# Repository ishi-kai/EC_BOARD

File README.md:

# This Board for Electrochromic Device Workshop.

- [Electrochromic Device Workshop:PDF](https://ishi-kai.org/assets/pdf/EC.pdf)
- [Electrochromic Device Workshop:PPTX](https://ishi-kai.org/assets/pdf/EC.pptx)

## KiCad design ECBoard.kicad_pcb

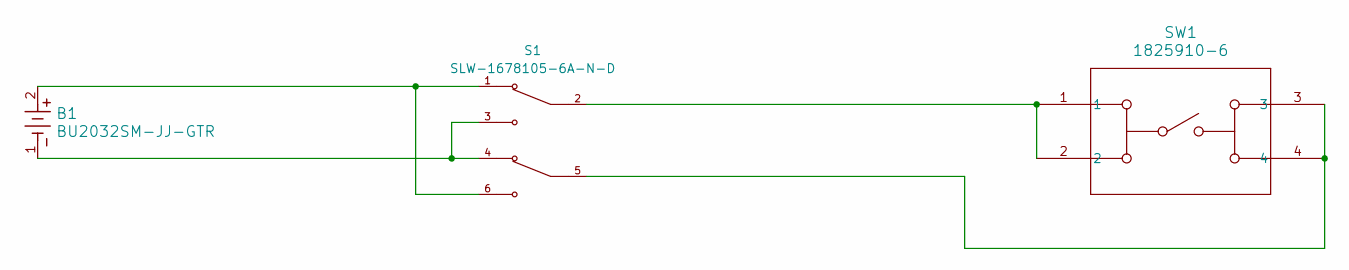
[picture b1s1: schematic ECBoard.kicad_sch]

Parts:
B1: BU2032SM-JJ-GTR; BU2032SM-JJ-GTR_MPD
S1: SLW-1678105-6A-N-D; SW_SLW-1678105-6A-N-D; PARTREV 1.01
SW1: 1825910-6; SW4_1825910-B_TEC

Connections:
unnamed: B1.1, S1.3, S1.4
unnamed: B1.2, S1.1, S1.6
unnamed: S1.2, SW1.1, SW1.2
unnamed: S1.5, SW1.3, SW1.4

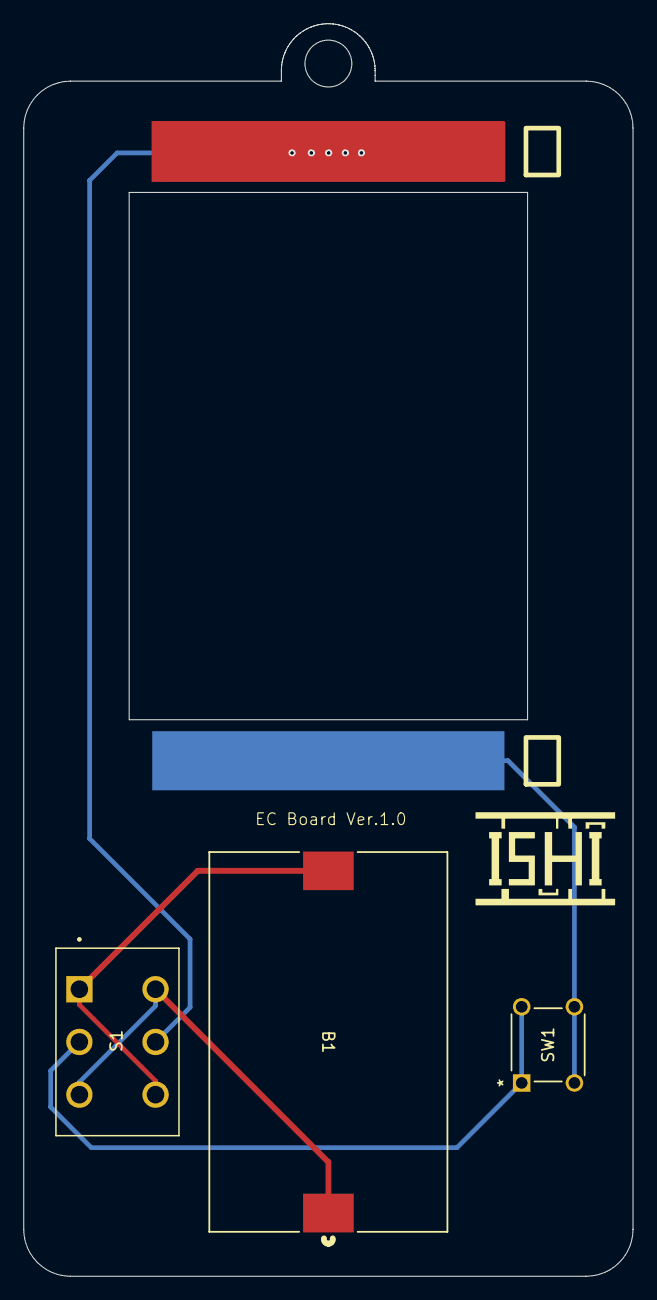
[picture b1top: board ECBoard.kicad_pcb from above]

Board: 2 copper layers, 52.0 x 106.9 mm, 3 parts (0 on the bottom side), 4 nets.
